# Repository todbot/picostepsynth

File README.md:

# picostepsynth

[more to come]

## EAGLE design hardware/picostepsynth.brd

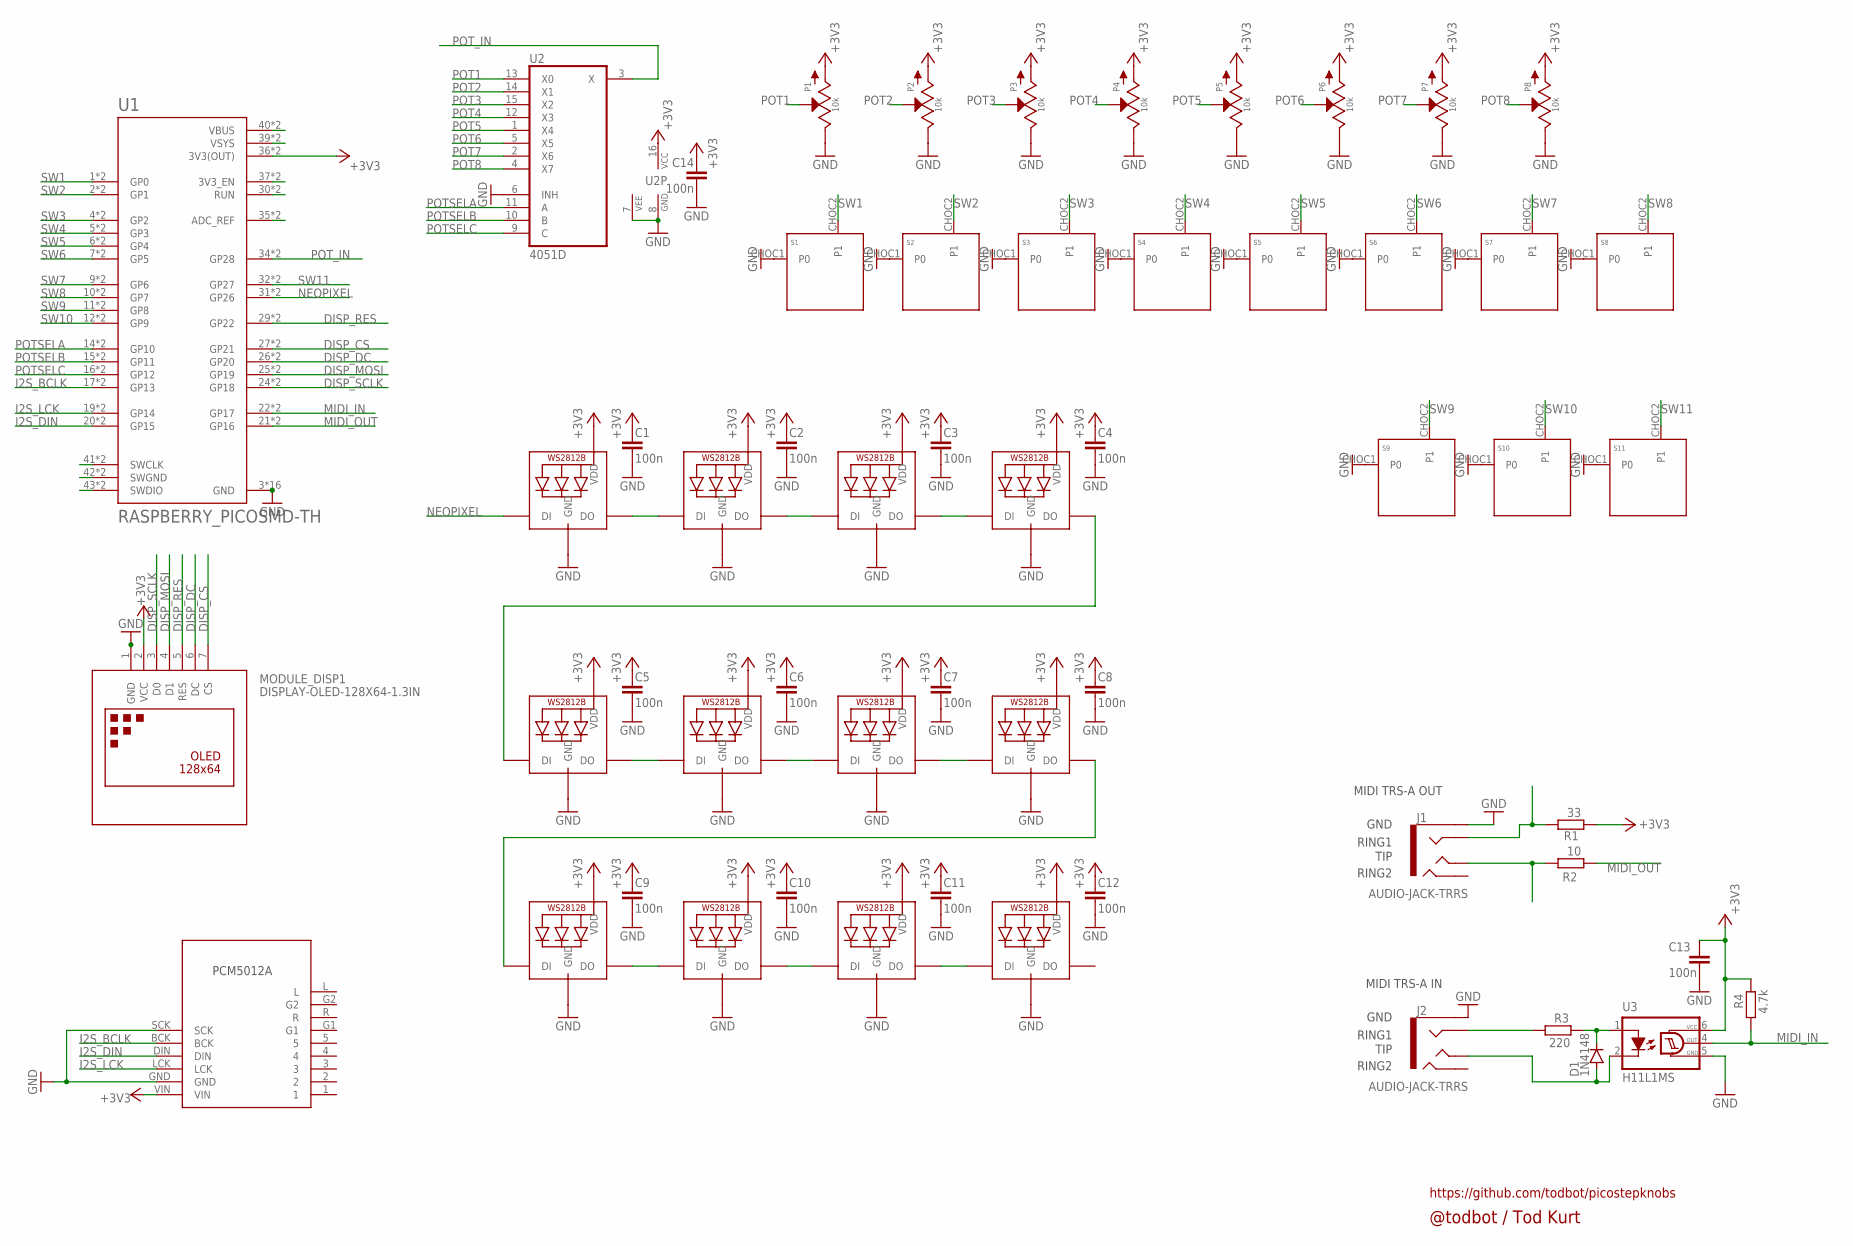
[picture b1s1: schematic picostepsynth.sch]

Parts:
C1, C2, C3, C4, C5, C6, C7, C8, C9, C10, C11, C12, C13, C14: 100n; C0805
D1: 1N4148; SOD123
J1: AUDIO-JACK-TRRS; PJ-320D_SPARKFUN; LCSC C431535
J2: AUDIO-JACK-TRRS; PJ-320D_SPARKFUN
LED1, LED2, LED3, LED4, LED5, LED6, LED7, LED8, LED9, LED10, LED11, LED12: WS2812B5050; WS2812B
MODULE_DISP1: DISPLAY-OLED-128X64-1.3IN
MODULE_PCM5102A: I2S_PCM_51XX_SOUNDCARD; I2S_PCM_5100_SOUNDCARD
P1, P2, P3, P4, P5, P6, P7, P8: 10k; OG-POTS_ALPS_POT_VERTICAL_WITHBIGKNOB
R1: 33; R0805
R2: 10; R0805
R3: 220; R0805
R4: 4.7k; R0805
S1, S2, S3, S4, S5, S6, S7, S8, S9, S10, S11: KEYSWITCH-PLAIN-CHOC-1U; CHOC-1U
U1: RASPBERRY_PICOSMD-TH; PICO-PKG
U2: 4051D; SO16
U3: H11L1MS; DIL6-SMD; MPN2 H11L1S; LCSC C78589

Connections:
+3V3: C1.1, C2.1, C3.1, C4.1, C5.1, C6.1, C7.1, C8.1, C9.1, C10.1, C11.1, C12.1, C13.1, C14.1, LED1.1-VDD (VDD), LED2.1-VDD (VDD), LED3.1-VDD (VDD), LED4.1-VDD (VDD), LED5.1-VDD (VDD), LED6.1-VDD (VDD), LED7.1-VDD (VDD), LED8.1-VDD (VDD), LED9.1-VDD (VDD), LED10.1-VDD (VDD), LED11.1-VDD (VDD), LED12.1-VDD (VDD), MODULE_DISP1.2 (VCC), MODULE_PCM5102A.VIN, P1.P$3 (A), P2.P$3 (A), P3.P$3 (A), P4.P$3 (A), P5.P$3 (A), P6.P$3 (A), P7.P$3 (A), P8.P$3 (A), R1.2, R4.1, U1.36 (3V3(OUT)), U1.P$36 (3V3(OUT)), U2.16 (VCC), U3.6 (VCC)
DISP_CS: MODULE_DISP1.7 (CS), U1.27 (GP21), U1.P$27 (GP21)
DISP_DC: MODULE_DISP1.6 (DC), U1.26 (GP20), U1.P$26 (GP20)
DISP_MOSI: MODULE_DISP1.4 (D1), U1.25 (GP19), U1.P$25 (GP19)
DISP_RES: MODULE_DISP1.5 (RES), U1.29 (GP22), U1.P$29 (GP22)
DISP_SCLK: MODULE_DISP1.3 (D0), U1.24 (GP18), U1.P$24 (GP18)
GND: C1.2, C2.2, C3.2, C4.2, C5.2, C6.2, C7.2, C8.2, C9.2, C10.2, C11.2, C12.2, C13.2, C14.2, J1.EARTH, J2.EARTH, LED1.3-GND (GND), LED2.3-GND (GND), LED3.3-GND (GND), LED4.3-GND (GND), LED5.3-GND (GND), LED6.3-GND (GND), LED7.3-GND (GND), LED8.3-GND (GND), LED9.3-GND (GND), LED10.3-GND (GND), LED11.3-GND (GND), LED12.3-GND (GND), MODULE_DISP1.1 (GND), MODULE_PCM5102A.GND, MODULE_PCM5102A.SCK, P1.P$1 (E), P2.P$1 (E), P3.P$1 (E), P4.P$1 (E), P5.P$1 (E), P6.P$1 (E), P7.P$1 (E), P8.P$1 (E), S1.CHOC1 (P0), S2.CHOC1 (P0), S3.CHOC1 (P0), S4.CHOC1 (P0), S5.CHOC1 (P0), S6.CHOC1 (P0), S7.CHOC1 (P0), S8.CHOC1 (P0), S9.CHOC1 (P0), S10.CHOC1 (P0), S11.CHOC1 (P0), U1.3 (GND), U1.8 (GND), U1.13 (GND), U1.18 (GND), U1.23 (GND), U1.28 (GND), U1.33 (GND), U1.38 (GND), U1.P$3 (GND), U1.P$8 (GND), U1.P$13 (GND), U1.P$18 (GND), U1.P$23 (GND), U1.P$28 (GND), U1.P$33 (GND), U1.P$38 (GND), U2.6 (INH), U2.7 (VEE), U2.8 (GND), U3.5 (GND)
I2S_BCLK: MODULE_PCM5102A.BCK, U1.17 (GP13), U1.P$17 (GP13)
I2S_DIN: MODULE_PCM5102A.DIN, U1.20 (GP15), U1.P$20 (GP15)
I2S_LCK: MODULE_PCM5102A.LCK, U1.19 (GP14), U1.P$19 (GP14)
MIDI_IN: R4.2, U1.22 (GP17), U1.P$22 (GP17), U3.4 (OUT)
MIDI_OUT: R2.2, U1.21 (GP16), U1.P$21 (GP16)
unnamed: LED1.2-DOUT (DO), LED2.4-DIN (DI)
unnamed: LED2.2-DOUT (DO), LED3.4-DIN (DI)
unnamed: U1.37 (3V3_EN), U1.P$37 (3V3_EN)
unnamed: LED3.2-DOUT (DO), LED4.4-DIN (DI)
unnamed: U1.30 (RUN), U1.P$30 (RUN)
unnamed: U1.35 (ADC_REF), U1.P$35 (ADC_REF)
unnamed: U1.40 (VBUS), U1.P$40 (VBUS)
unnamed: U1.39 (VSYS), U1.P$39 (VSYS)
unnamed: J1.TIP, R2.1
unnamed: LED4.2-DOUT (DO), LED5.4-DIN (DI)
unnamed: LED5.2-DOUT (DO), LED6.4-DIN (DI)
unnamed: LED6.2-DOUT (DO), LED7.4-DIN (DI)
unnamed: LED7.2-DOUT (DO), LED8.4-DIN (DI)
unnamed: LED9.2-DOUT (DO), LED10.4-DIN (DI)
unnamed: LED10.2-DOUT (DO), LED11.4-DIN (DI)
unnamed: LED11.2-DOUT (DO), LED12.4-DIN (DI)
unnamed: LED8.2-DOUT (DO), LED9.4-DIN (DI)
unnamed: U1.41 (SWCLK), U1.P$41 (SWCLK)
unnamed: U1.42 (SWGND), U1.P$42 (SWGND)
unnamed: U1.43 (SWDIO), U1.P$43 (SWDIO)
unnamed: J1.RING1, R1.1
unnamed: D1.C, R3.1, U3.1 (A)
unnamed: D1.A, J2.TIP, U3.2 (C)
unnamed: J2.RING1, R3.2
NEOPIXEL: LED1.4-DIN (DI), U1.31 (GP26), U1.P$31 (GP26)
POT1: P1.P$2 (S), U2.13 (X0)
POT2: P2.P$2 (S), U2.14 (X1)
POT3: P3.P$2 (S), U2.15 (X2)
POT4: P4.P$2 (S), U2.12 (X3)
POT5: P5.P$2 (S), U2.1 (X4)
POT6: P6.P$2 (S), U2.5 (X5)
POT7: P7.P$2 (S), U2.2 (X6)
POT8: P8.P$2 (S), U2.4 (X7)
POTSELA: U1.14 (GP10), U1.P$14 (GP10), U2.11 (A)
POTSELB: U1.15 (GP11), U1.P$15 (GP11), U2.10 (B)
POTSELC: U1.16 (GP12), U1.P$16 (GP12), U2.9 (C)
POT_IN: U1.34 (GP28), U1.P$34 (GP28), U2.3 (X)
SW1: S1.CHOC2 (P1), U1.1 (GP0), U1.P$1 (GP0)
SW2: S2.CHOC2 (P1), U1.2 (GP1), U1.P$2 (GP1)
SW3: S3.CHOC2 (P1), U1.4 (GP2), U1.P$4 (GP2)
SW4: S4.CHOC2 (P1), U1.5 (GP3), U1.P$5 (GP3)
SW5: S5.CHOC2 (P1), U1.6 (GP4), U1.P$6 (GP4)
SW6: S6.CHOC2 (P1), U1.7 (GP5), U1.P$7 (GP5)
SW7: S7.CHOC2 (P1), U1.9 (GP6), U1.P$9 (GP6)
SW8: S8.CHOC2 (P1), U1.10 (GP7), U1.P$10 (GP7)
SW9: S9.CHOC2 (P1), U1.11 (GP8), U1.P$11 (GP8)
SW10: S10.CHOC2 (P1), U1.12 (GP9), U1.P$12 (GP9)
SW11: S11.CHOC2 (P1), U1.32 (GP27), U1.P$32 (GP27)

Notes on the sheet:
@todbot / Tod Kurt
https://github.com/todbot/picostepknobs
MIDI TRS-A OUT
RING2
RING1
GND
TIP
MIDI TRS-A IN
PCM5012A

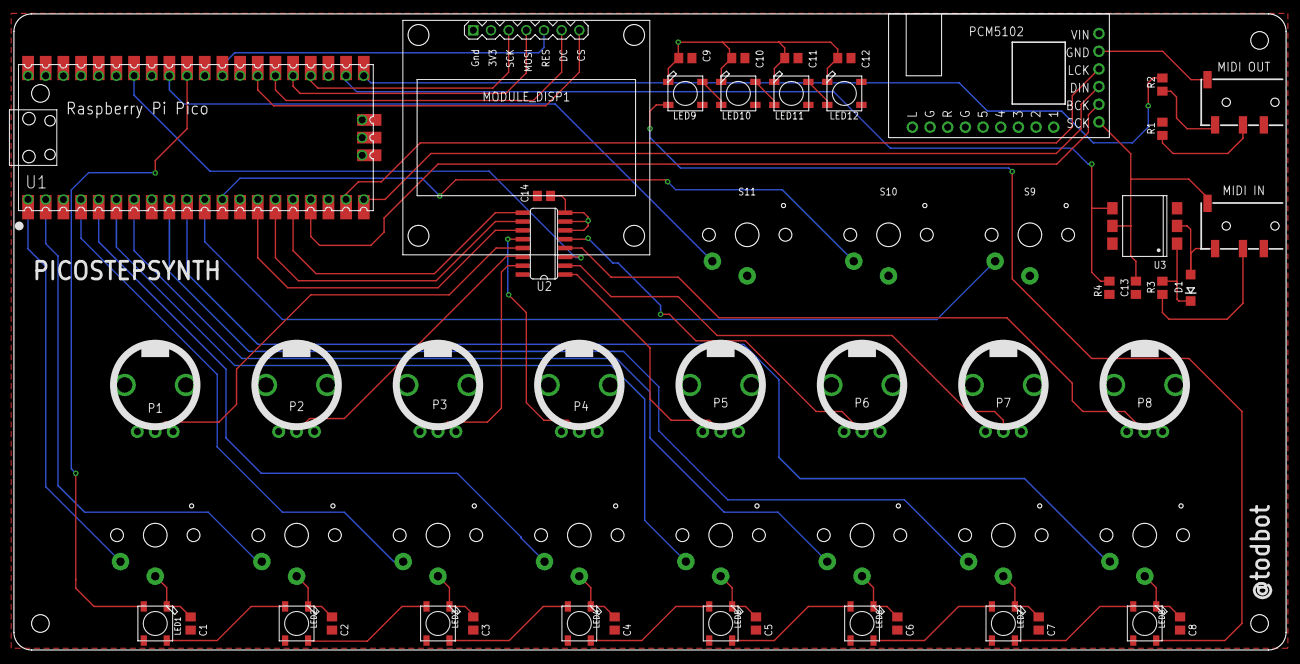
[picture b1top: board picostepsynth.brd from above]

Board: 2 copper layers, 182.7 x 91.2 mm, 57 parts (0 on the bottom side), 60 nets.

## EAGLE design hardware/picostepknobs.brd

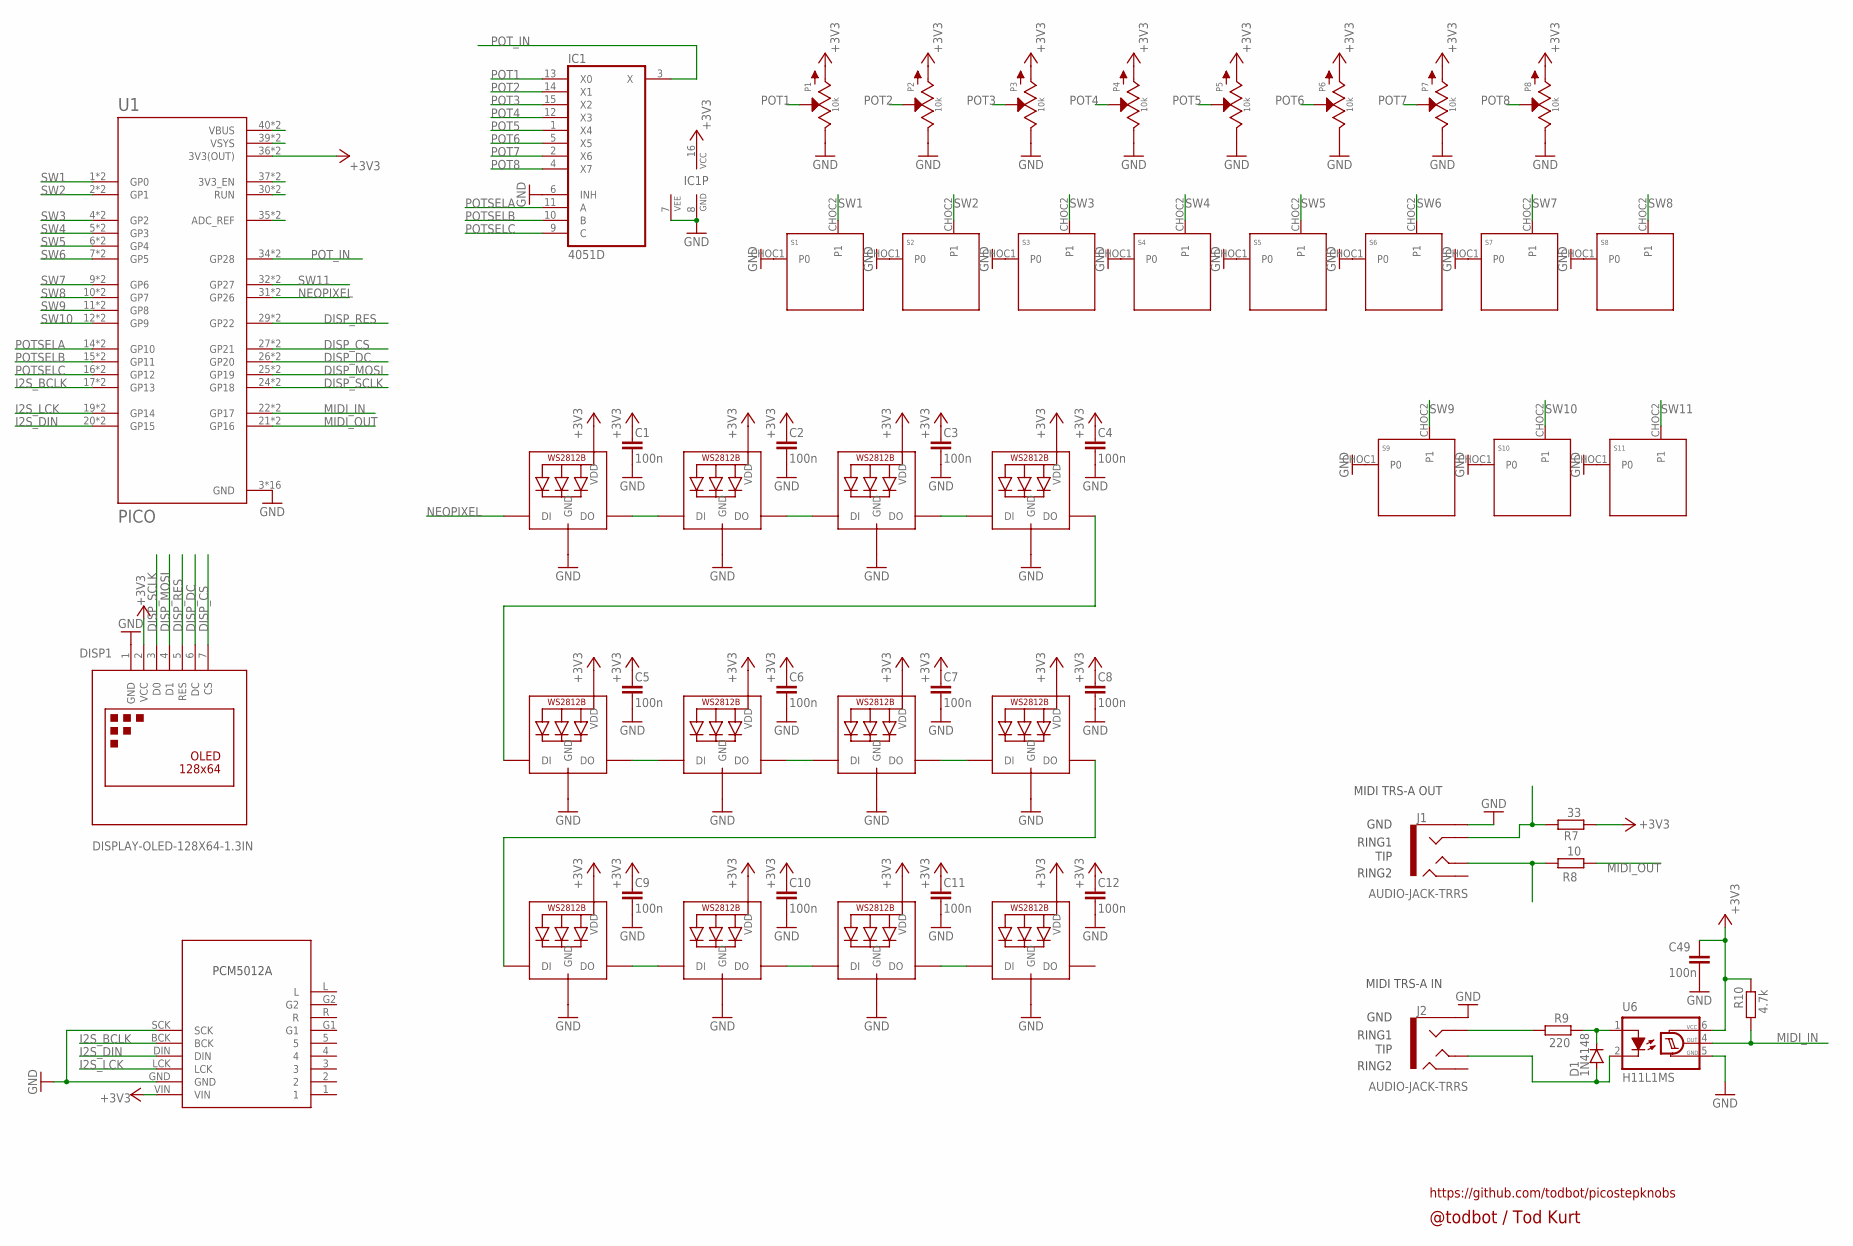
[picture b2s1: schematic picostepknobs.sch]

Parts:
C1, C2, C3, C4, C5, C6, C7, C8, C9, C10, C11, C12, C49: 100n; C0805
D1: 1N4148; SOD123
DISP1: DISPLAY-OLED-128X64-1.3IN
IC1: 4051D; SO16
J1: AUDIO-JACK-TRRS; PJ-320D_SPARKFUN; LCSC C431535
J2: AUDIO-JACK-TRRS; PJ-320D_SPARKFUN
LED1, LED2, LED3, LED4, LED5, LED6, LED7, LED8, LED9, LED10, LED11, LED12: WS2812B3535; LED3535
P1, P2, P3, P4, P5, P6, P7, P8: 10k; OG-POTS_ALPS_POT_VERTICAL_WITHBIGKNOB
PCM5102A: I2S_PCM_51XX_SOUNDCARD; I2S_PCM_5100_SOUNDCARD
R7: 33; R0805
R8: 10; R0805
R9: 220; R0805
R10: 4.7k; R0805
S1, S2, S3, S4, S5, S6, S7, S8, S9, S10, S11: KEYSWITCH-PLAIN-CHOC-1U; CHOC-1U
U1: PICO; PICO-PKG-NO_DEBUG
U6: H11L1MS; DIL6-SMD; MPN2 H11L1S; LCSC C78589

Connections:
+3V3: C1.1, C2.1, C3.1, C4.1, C5.1, C6.1, C7.1, C8.1, C9.1, C10.1, C11.1, C12.1, C49.1, DISP1.2 (VCC), IC1.16 (VCC), LED1.2 (VDD), LED2.2 (VDD), LED3.2 (VDD), LED4.2 (VDD), LED5.2 (VDD), LED6.2 (VDD), LED7.2 (VDD), LED8.2 (VDD), LED9.2 (VDD), LED10.2 (VDD), LED11.2 (VDD), LED12.2 (VDD), P1.P$3 (A), P2.P$3 (A), P3.P$3 (A), P4.P$3 (A), P5.P$3 (A), P6.P$3 (A), P7.P$3 (A), P8.P$3 (A), PCM5102A.VIN, R7.2, R10.1, U1.36 (3V3(OUT)), U1.P$36 (3V3(OUT)), U6.6 (VCC)
DISP_CS: DISP1.7 (CS), U1.27 (GP21), U1.P$27 (GP21)
DISP_DC: DISP1.6 (DC), U1.26 (GP20), U1.P$26 (GP20)
DISP_MOSI: DISP1.4 (D1), U1.25 (GP19), U1.P$25 (GP19)
DISP_RES: DISP1.5 (RES), U1.29 (GP22), U1.P$29 (GP22)
DISP_SCLK: DISP1.3 (D0), U1.24 (GP18), U1.P$24 (GP18)
GND: C1.2, C2.2, C3.2, C4.2, C5.2, C6.2, C7.2, C8.2, C9.2, C10.2, C11.2, C12.2, C49.2, DISP1.1 (GND), IC1.6 (INH), IC1.7 (VEE), IC1.8 (GND), J1.EARTH, J2.EARTH, LED1.4 (GND), LED2.4 (GND), LED3.4 (GND), LED4.4 (GND), LED5.4 (GND), LED6.4 (GND), LED7.4 (GND), LED8.4 (GND), LED9.4 (GND), LED10.4 (GND), LED11.4 (GND), LED12.4 (GND), P1.P$1 (E), P2.P$1 (E), P3.P$1 (E), P4.P$1 (E), P5.P$1 (E), P6.P$1 (E), P7.P$1 (E), P8.P$1 (E), PCM5102A.GND, PCM5102A.SCK, S1.CHOC1 (P0), S2.CHOC1 (P0), S3.CHOC1 (P0), S4.CHOC1 (P0), S5.CHOC1 (P0), S6.CHOC1 (P0), S7.CHOC1 (P0), S8.CHOC1 (P0), S9.CHOC1 (P0), S10.CHOC1 (P0), S11.CHOC1 (P0), U1.3 (GND), U1.8 (GND), U1.13 (GND), U1.18 (GND), U1.23 (GND), U1.28 (GND), U1.33 (GND), U1.38 (GND), U1.P$3 (GND), U1.P$8 (GND), U1.P$13 (GND), U1.P$18 (GND), U1.P$23 (GND), U1.P$28 (GND), U1.P$33 (GND), U1.P$38 (GND), U6.5 (GND)
I2S_BCLK: PCM5102A.BCK, U1.17 (GP13), U1.P$17 (GP13)
I2S_DIN: PCM5102A.DIN, U1.20 (GP15), U1.P$20 (GP15)
I2S_LCK: PCM5102A.LCK, U1.19 (GP14), U1.P$19 (GP14)
MIDI_IN: R10.2, U1.22 (GP17), U1.P$22 (GP17), U6.4 (OUT)
MIDI_OUT: R8.2, U1.21 (GP16), U1.P$21 (GP16)
unnamed: LED1.3 (DO), LED2.1 (DI)
unnamed: LED2.3 (DO), LED3.1 (DI)
unnamed: U1.37 (3V3_EN), U1.P$37 (3V3_EN)
unnamed: LED3.3 (DO), LED4.1 (DI)
unnamed: U1.30 (RUN), U1.P$30 (RUN)
unnamed: U1.35 (ADC_REF), U1.P$35 (ADC_REF)
unnamed: U1.40 (VBUS), U1.P$40 (VBUS)
unnamed: U1.39 (VSYS), U1.P$39 (VSYS)
unnamed: J1.TIP, R8.1
unnamed: LED4.3 (DO), LED5.1 (DI)
unnamed: LED5.3 (DO), LED6.1 (DI)
unnamed: LED6.3 (DO), LED7.1 (DI)
unnamed: LED7.3 (DO), LED8.1 (DI)
unnamed: LED9.3 (DO), LED10.1 (DI)
unnamed: LED10.3 (DO), LED11.1 (DI)
unnamed: LED11.3 (DO), LED12.1 (DI)
unnamed: LED8.3 (DO), LED9.1 (DI)
unnamed: J1.RING1, R7.1
unnamed: D1.C, R9.1, U6.1 (A)
unnamed: D1.A, J2.TIP, U6.2 (C)
unnamed: J2.RING1, R9.2
NEOPIXEL: LED1.1 (DI), U1.31 (GP26), U1.P$31 (GP26)
POT1: IC1.13 (X0), P1.P$2 (S)
POT2: IC1.14 (X1), P2.P$2 (S)
POT3: IC1.15 (X2), P3.P$2 (S)
POT4: IC1.12 (X3), P4.P$2 (S)
POT5: IC1.1 (X4), P5.P$2 (S)
POT6: IC1.5 (X5), P6.P$2 (S)
POT7: IC1.2 (X6), P7.P$2 (S)
POT8: IC1.4 (X7), P8.P$2 (S)
POTSELA: IC1.11 (A), U1.14 (GP10), U1.P$14 (GP10)
POTSELB: IC1.10 (B), U1.15 (GP11), U1.P$15 (GP11)
POTSELC: IC1.9 (C), U1.16 (GP12), U1.P$16 (GP12)
POT_IN: IC1.3 (X), U1.34 (GP28), U1.P$34 (GP28)
SW1: S1.CHOC2 (P1), U1.1 (GP0), U1.P$1 (GP0)
SW2: S2.CHOC2 (P1), U1.2 (GP1), U1.P$2 (GP1)
SW3: S3.CHOC2 (P1), U1.4 (GP2), U1.P$4 (GP2)
SW4: S4.CHOC2 (P1), U1.5 (GP3), U1.P$5 (GP3)
SW5: S5.CHOC2 (P1), U1.6 (GP4), U1.P$6 (GP4)
SW6: S6.CHOC2 (P1), U1.7 (GP5), U1.P$7 (GP5)
SW7: S7.CHOC2 (P1), U1.9 (GP6), U1.P$9 (GP6)
SW8: S8.CHOC2 (P1), U1.10 (GP7), U1.P$10 (GP7)
SW9: S9.CHOC2 (P1), U1.11 (GP8), U1.P$11 (GP8)
SW10: S10.CHOC2 (P1), U1.12 (GP9), U1.P$12 (GP9)
SW11: S11.CHOC2 (P1), U1.32 (GP27), U1.P$32 (GP27)

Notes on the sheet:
@todbot / Tod Kurt
https://github.com/todbot/picostepknobs
MIDI TRS-A OUT
RING2
RING1
GND
TIP
MIDI TRS-A IN
PCM5012A

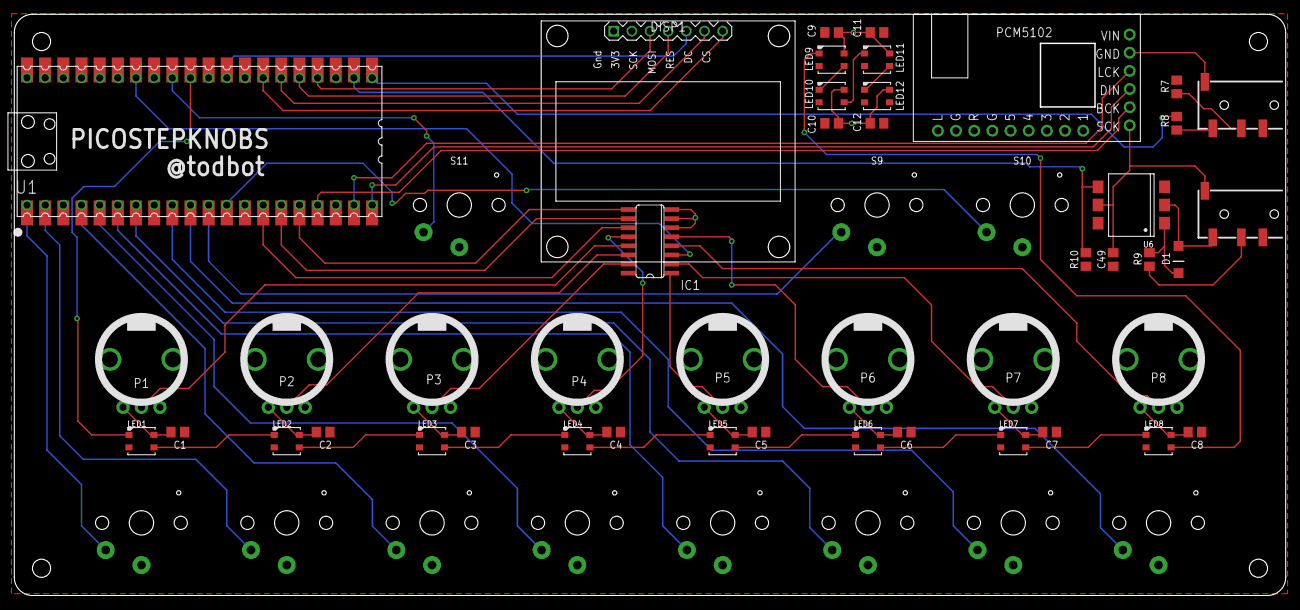
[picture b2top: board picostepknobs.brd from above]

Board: 2 copper layers, 177.6 x 81.1 mm, 56 parts (0 on the bottom side), 57 nets.

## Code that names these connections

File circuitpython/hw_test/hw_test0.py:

# hw_test0.py -- bring up PICOSTEPKNOBS hardware, just to see if we can
import time
import board
import busio
import audiobusio
import digitalio
import keypad
import neopixel
import displayio
import terminalio
from adafruit_display_text import label
import adafruit_displayio_sh1106

key_pins = (board.GP0, board.GP1, board.GP2, board.GP3, board.GP4,
            board.GP5, board.GP6, board.GP7, board.GP8, board.GP9, board.GP27)

potselA_pin = board.GP10
potselB_pin = board.GP11
potselC_pin = board.GP12

i2s_lck_pin = board.GP14
i2s_bck_pin = board.GP13
i2s_dat_pin = board.GP15

midi_tx_pin = board.GP16
midi_rx_pin = board.GP17

disp_sclk = board.GP18
disp_mosi = board.GP19
disp_dc   = board.GP20
disp_cs   = board.GP21
disp_res  = board.GP22  # or could use 10uF/10k RC circuit instead of GPIO

neopixel_pin = board.GP26
led_pin = board.GP25 # built-in LED on Pico
pot_pin = board.GP28


# Audio output setup
audio = audiobusio.I2SOut(bit_clock=i2s_bck_pin, word_select=i2s_lck_pin, data=i2s_dat_pin)

# Display setup
displayio.release_displays()
dw,dh = 132,64
spi = busio.SPI(clock=disp_sclk, MOSI=disp_mosi)
display_bus = displayio.FourWire(spi, command = disp_dc, chip_select = disp_cs, reset=disp_res)
display = adafruit_displayio_sh1106.SH1106(display_bus, width=dw, height=dh, colstart=3)

# MIDI setup
midi_uart = busio.UART(tx=midi_tx_pin, rx=midi_rx_pin, baudrate=31250) # timeout=midi_timeout)

# LED setup
led = digitalio.DigitalInOut(led_pin)
led.switch_to_output(value=True)
#leds = neopixel.NeoPixel(neopixel_pin, 1, brightness=0.2)

# Keys setup
keys = keypad.Keys(key_pins, value_when_pressed=False, pull=True)


print("hello")
time.sleep(2)

while True:
    print("01234567890123456789")
    print("hi %3.2f" % time.monotonic())
    led.value = not led.value
    time.sleep(0.15)

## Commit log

2023-05-18 first
2023-05-18 brd layout
2023-05-20 brd: moved display to left
2023-05-20 fix oled display helper notes on silkscreen
2023-05-22 readme
2023-05-22 oops forgot bypass cap on 4051
2023-05-25 it is working a little
2023-05-25 project rename
2023-05-26 keep proto version for posterity
2023-05-27 brd: make larger to support a proper case
2023-07-01 more experiments with stepsynth1 on picostepknobs board
2025-10-03 added stepsynth1 first version
